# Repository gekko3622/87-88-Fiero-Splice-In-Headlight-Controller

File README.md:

# 1987-1988 Pontiac Fiero Headlight Motor Controller
**PCB Designed by Ryan Blanchard 4.2024**\
**Based On A Project by WalkerTexan** (See credits section for details and link)\
**FOR NON-COMMERCIAL USE ONLY.**

**NEW! V2.2 has been added which supports internal ATC fuses for the motor power inputs.**\
**V2.1 has been retained in the repository for those who want to use external inline fuses or don't feel the need to.**

\
**Note:** This is my personal PCB, based on version 2.0. The files contained in this project are version 2.2 and 2.1.\
V2.2 adds provisions for standard ATC fuses on the main 12V lines to the motors. Other minor trace routing optimizations were added as well.\
V2.1 is electrically identical to V2.0. The only changes made were to reposition and enlarge some of the silkscreen label text for legibility.

## Intro
This project is a PCB implementation of WalkerTexan's "Fiero Headlight Controller".\
I started this 	project after getting frustrated with the cost and questionable reliability of used modules.\
While there are also new production versions of the original module available now, I found the cost to be way too high.

## Purpose and Origin
I started this project to replace the second failed module in my 87 Pontiac Fiero.\
It started as a basic DIY project and grew into a proper PCB design after my prototype proved to be reliable.

Pictured here is my original DIY prototype. The PCB version is night-and-day BEAUTIFUL compared to this thing.

## Repository Contents

**Items 2 and 3 are now contained within version numbered folders.**

**1. Arduino Nano Program**
- WalkerTexan's code for the Arduino Nano.\
This MUST be programmed onto the Arduino for the module to function. The same file is used for V2.2 and V2.1.

**2. Gerber Files (For Production)**
- These are the files that must be provided to a fabricator to produce a PCB.\
  **VERY IMPORTANT:** This PCB MUST be produced with 2 Oz copper weight in order to meet power handling requirements.\
  The provided gerber files will produce an electrically identical copy of the PCB installed in my own car.

  The provided Zip file can be directly submitted to a fabricator and contains all of the other individual files in this folder.

**3. KiCad Project Files**
- These are my original KiCad 8.0 project files.\
  You will need these if you intend to make any alterations to the PCB's design.

## Installation Location
This module is designed to be installed under the hood, in the area around the brake master cylinder.\
This allows for easier access and makes it possible to install without damaging the original connectors.\
NOTE: Installing this module will require you to cut and slice a new connector onto the original front wiring harness.

## Wiring Guide
You will need to provide two sets of waterproof automotive connectos for this project.\
For the sake of this writeup, I'll assume you have 5-pin and 4-pin connector sets.\
Connector/pin numbers are based on the labels printed on my version of the PCB (See image below).\
Wire colors give are for the wires contained in the factory wiring harness, which runs inside the frunk, driver side.\
If you make changes, you will need to determine your own wiring scheme.

**SAFETY WARNING: Please splice into the wiring harness after any fusible links. They are there for a reason.**

### To Wiring Harness
	
C1-1  -  Connect to red wire on harness. (there are two, both will be used)\
C1-2  -  Connect to ground. I recommend running a new ground wire. The harness contains MANY black ground wires.\
C1-3  -  Connect to white wire on harness.\
C1-4  -  Connect to other red wire on harness.\
C1-5  -  Connect to yellow wire on wiring harness.

### To Headlight Motors
		
C2-1  -  Light Green/Black\
C2-2  -  Gray/Black\
C2-3  -  Dark Green\
C2-4  -  Gray

**You may want to run new wires and connectors to the headlight motors to preserve original wiring.**

I used a generic equivalent of AC Delco PT724.\
The connector has notches cut into the plastic pin barrels. These do not match the notches on the headlight motor connector.\
I solved this problem by heating a knife with a lighter and cutting my own matching notches into the new connectors.

If you go this route, cut the new notches as indicated in red on this image:\

## Component List
See BOM.xlsx for a full list of required components.

## Enclosure
The PCB is intended to be installed within a water-resistant project box.\
The specific box I used is this: https://www.amazon.com/dp/B075WZFWFV?th=1  
Any enclosure with space for a 170mm x 110mm PCB could be used, though mounting hole pattern should be considered.\
Keep in mind there needs to be some space for the wiring too.

**PCB Mounting Holes (center to center):** 160 mm x 90 mm

## Modifications to Original Source
1. Recreated the schematic diagram in KiCad.
2. Designed a PCB based on the schematic.
3. Substituted the 5V relays for an alternate part with higher current rating.
4. Added detachable headers and connectors for connecting to the car's wiring.

## Credits
The electrical schematic and Arduino code this project is based on were created by WalkerTexan.\
See his original project here: https://www.hackster.io/walkertexan/fiero-headlight-controller-8eaa4c

KiCad Schematic and PCB Layout/Design by Ryan Blanchard.

## License
This project is published under the Creative Commons Attribution-NonCommercial-ShareAlike 4.0 International license.\
Use of this project for commercial purposes is prohibited.

For full details, see the license file.

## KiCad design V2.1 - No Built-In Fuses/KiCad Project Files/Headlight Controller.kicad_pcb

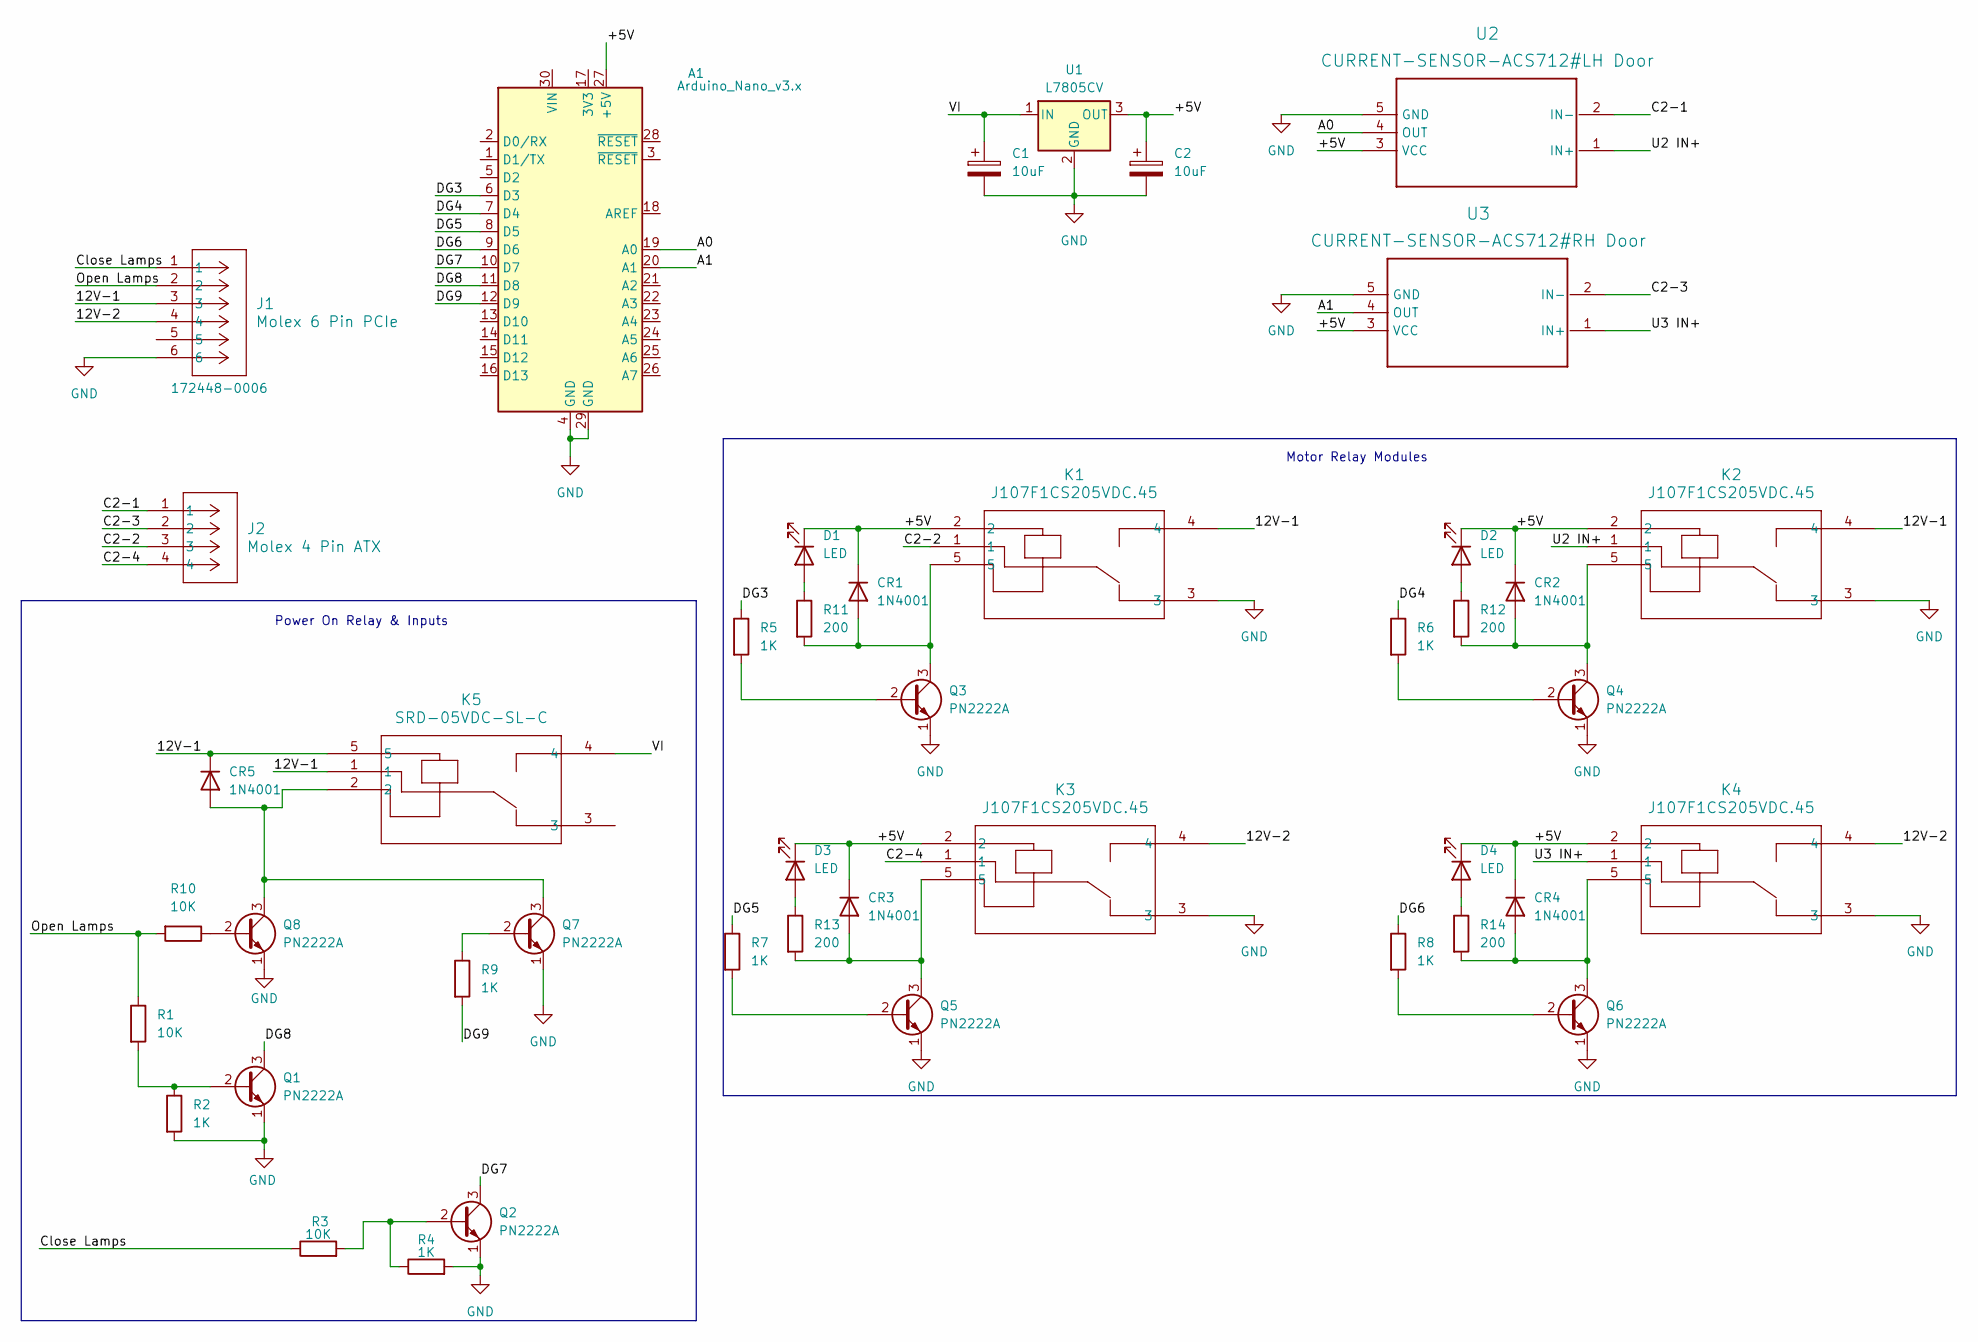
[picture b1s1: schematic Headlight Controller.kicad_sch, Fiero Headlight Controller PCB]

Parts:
A1: Arduino_Nano_v3.x; Arduino_Nano
C1, C2: 10uF; CAP-TH_BD5.0-P2.00-D0.8-FD
CR1, CR2, CR3, CR4, CR5: 1N4001; DIODE-1N4001
D1, D2, D3, D4: LED; LED-5MM-5MM
J1: Molex 6 Pin PCIe; 6 Pin PCIe
J2: Molex 4 Pin ATX; 4 Pin ATX
K1, K2, K3, K4: J107F1CS205VDC.45; JQC-3FF-S-Z
K5: SRD-05VDC-SL-C; JQC-3FF-S-Z
Q1, Q2, Q3, Q4, Q5, Q6, Q7, Q8: PN2222A; 2N2222A
R1, R3, R10: 10K; Resistors
R2, R4, R5, R6, R7, R8, R9: 1K; Resistors
R11, R12, R13, R14: 200; Resistors
U1: L7805CV; L7805
U2: CURRENT-SENSOR-ACS712#LH Door; ACS712_A
U3: CURRENT-SENSOR-ACS712#RH Door; ACS712_A

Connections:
/12V-1: CR5.C (K), J1.3, K1.4, K2.4, K5.1, K5.5
/12V-2: J1.4, K3.4, K4.4
/+5V: A1.27 (+5V), C2.1, CR1.C (K), CR2.C (K), CR3.C (K), CR4.C (K), D1.1 (K), D2.1 (K), D3.1 (K), D4.1 (K), K1.2, K2.2, K3.2, K4.2, U1.3 (OUT), U2.3 (VCC), U3.3 (VCC)
/A0: A1.19 (A0), U2.4 (OUT)
/A1: A1.20 (A1), U3.4 (OUT)
/C2-1: J2.1, U2.2 (IN-)
/C2-2: J2.3, K1.1
/C2-3: J2.2, U3.2 (IN-)
/C2-4: J2.4, K3.1
/Close Lamps: J1.1, R3.1
/DG3: A1.6 (D3), R5.1
/DG4: A1.7 (D4), R6.1
/DG5: A1.8 (D5), R7.1
/DG6: A1.9 (D6), R8.1
/DG7: A1.10 (D7), Q2.3 (C)
/DG8: A1.11 (D8), Q1.3 (C)
/DG9: A1.12 (D9), R9.2
/Open Lamps: J1.2, R1.1, R10.2
/U2 IN+: K2.1, U2.1 (IN+)
/U3 IN+: K4.1, U3.1 (IN+)
/VI: C1.1, K5.4, U1.1 (IN)
GND: A1.4 (GND), A1.29 (GND), C1.2, C2.2, J1.6, K1.3, K2.3, K3.3, K4.3, Q1.1 (E), Q2.1 (E), Q3.1 (E), Q4.1 (E), Q5.1 (E), Q6.1 (E), Q7.1 (E), Q8.1 (E), R2.2, R4.2, U1.2 (GND), U2.5 (GND), U3.5 (GND)
unnamed: D1.2 (A), R11.1
unnamed: D2.2 (A), R12.1
unnamed: D3.2 (A), R13.1
unnamed: D4.2 (A), R14.1
unnamed: Q1.2 (B), R1.2, R2.1
unnamed: Q2.2 (B), R3.2, R4.1
unnamed: Q3.2 (B), R5.2
unnamed: CR1.A, K1.5, Q3.3 (C), R11.2
unnamed: Q4.2 (B), R6.2
unnamed: CR2.A, K2.5, Q4.3 (C), R12.2
unnamed: Q5.2 (B), R7.2
unnamed: CR3.A, K3.5, Q5.3 (C), R13.2
unnamed: Q6.2 (B), R8.2
unnamed: CR4.A, K4.5, Q6.3 (C), R14.2
unnamed: Q7.2 (B), R9.1
unnamed: CR5.A, K5.2, Q7.3 (C), Q8.3 (C)
unnamed: Q8.2 (B), R10.1

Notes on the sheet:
Motor Relay Modules
Power On Relay & Inputs

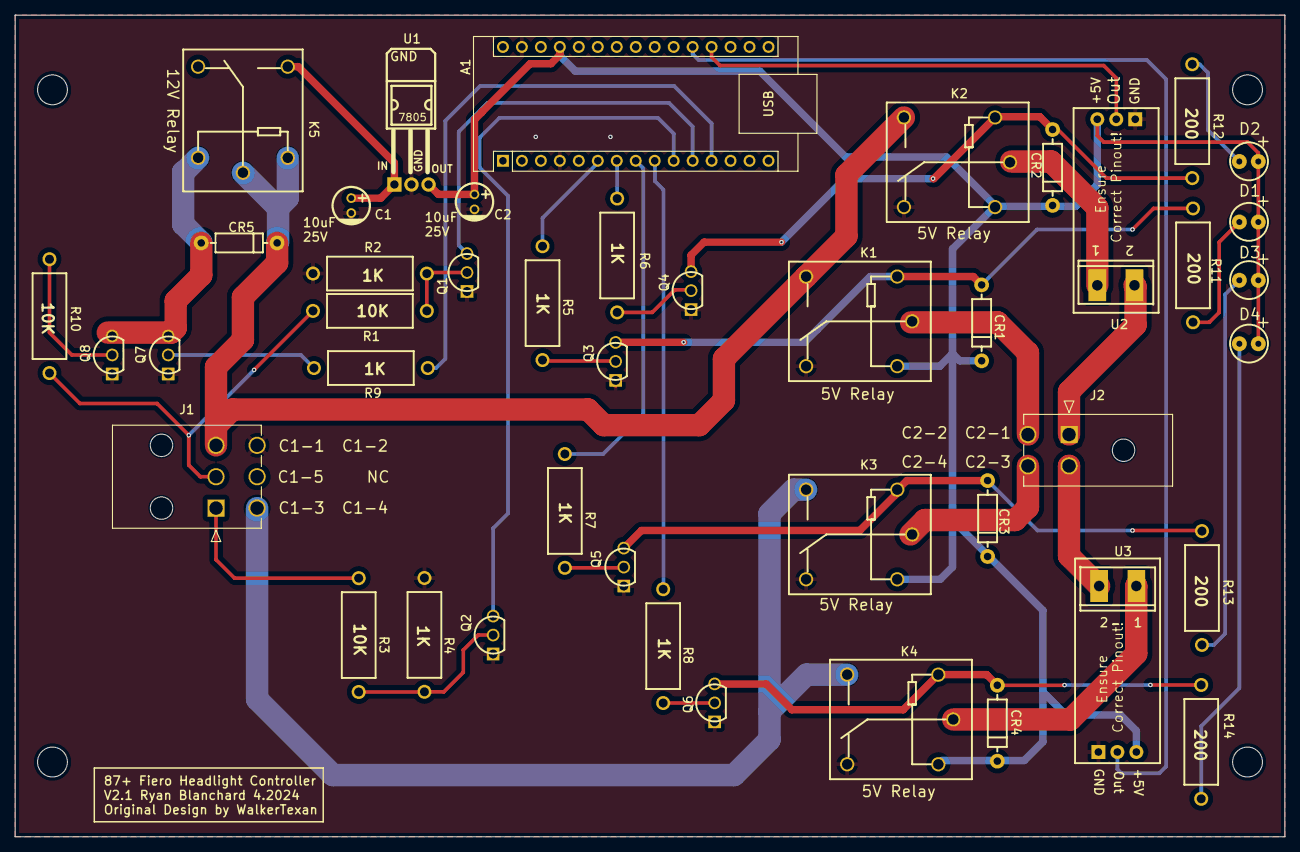
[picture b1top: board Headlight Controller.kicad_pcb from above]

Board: 2 copper layers, 170.0 x 110.0 mm, 44 parts (0 on the bottom side), 39 nets.

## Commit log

2024-04-12 Add files via upload
    First file upload. Contains only the base project files and gerber files.
2024-04-12 Create README.md
    Add ReadMe documentation.
2024-04-12 Add License
    Add the Creative Commons CC BY-NC-SA 4.0 license.
2024-04-12 Update README.md
    Added enclosure information, minor tweaks.
2024-04-12 Update README.md
    Updated BOM information. Removed reference to wiki, as I won't be using it.
2024-04-12 Added BOM.xlsx
    Added the BOM.
2024-04-12 Added Arduino Nano Program
2024-04-13 Updated BOM
2024-04-14 Updated BOM: pin headers/Alternative Arduino
2024-04-14 Added V2.2 - Internal Fuses
    Version 2.2 has mounting holes to solder ATC fuses directly or in a holder.
    V2.1 retained for those who would prefer to use inline external fuses.
2024-04-14 Removed unnecessary backup files
2024-04-14 Update README.md
    Clarification of difference between 2.2 and 2.1
2024-04-15 Removed old/unnecessary files
